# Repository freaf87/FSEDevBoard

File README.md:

Rpi Autonomous Car PCB 
====================
This board bring those additional functions below to the Raspberry pi:

	 - Analog Digital Converter with MCP3008 (8)
	 - DC Brushed Motor driver (2) with TB6612FNG
	 - Level converted IOs (5V <-> 3.3V) (8)
     - 16-channel, 12-bit PWM with PCA9685
     - RGB LED (1)
     - Pushbutton (1)

Top                                                                      |  Bottom
:-----------------------------------------------------------------------:|:--------------------------------------------------------------:
  |  

Author: Frederic Afadjigla, 2018

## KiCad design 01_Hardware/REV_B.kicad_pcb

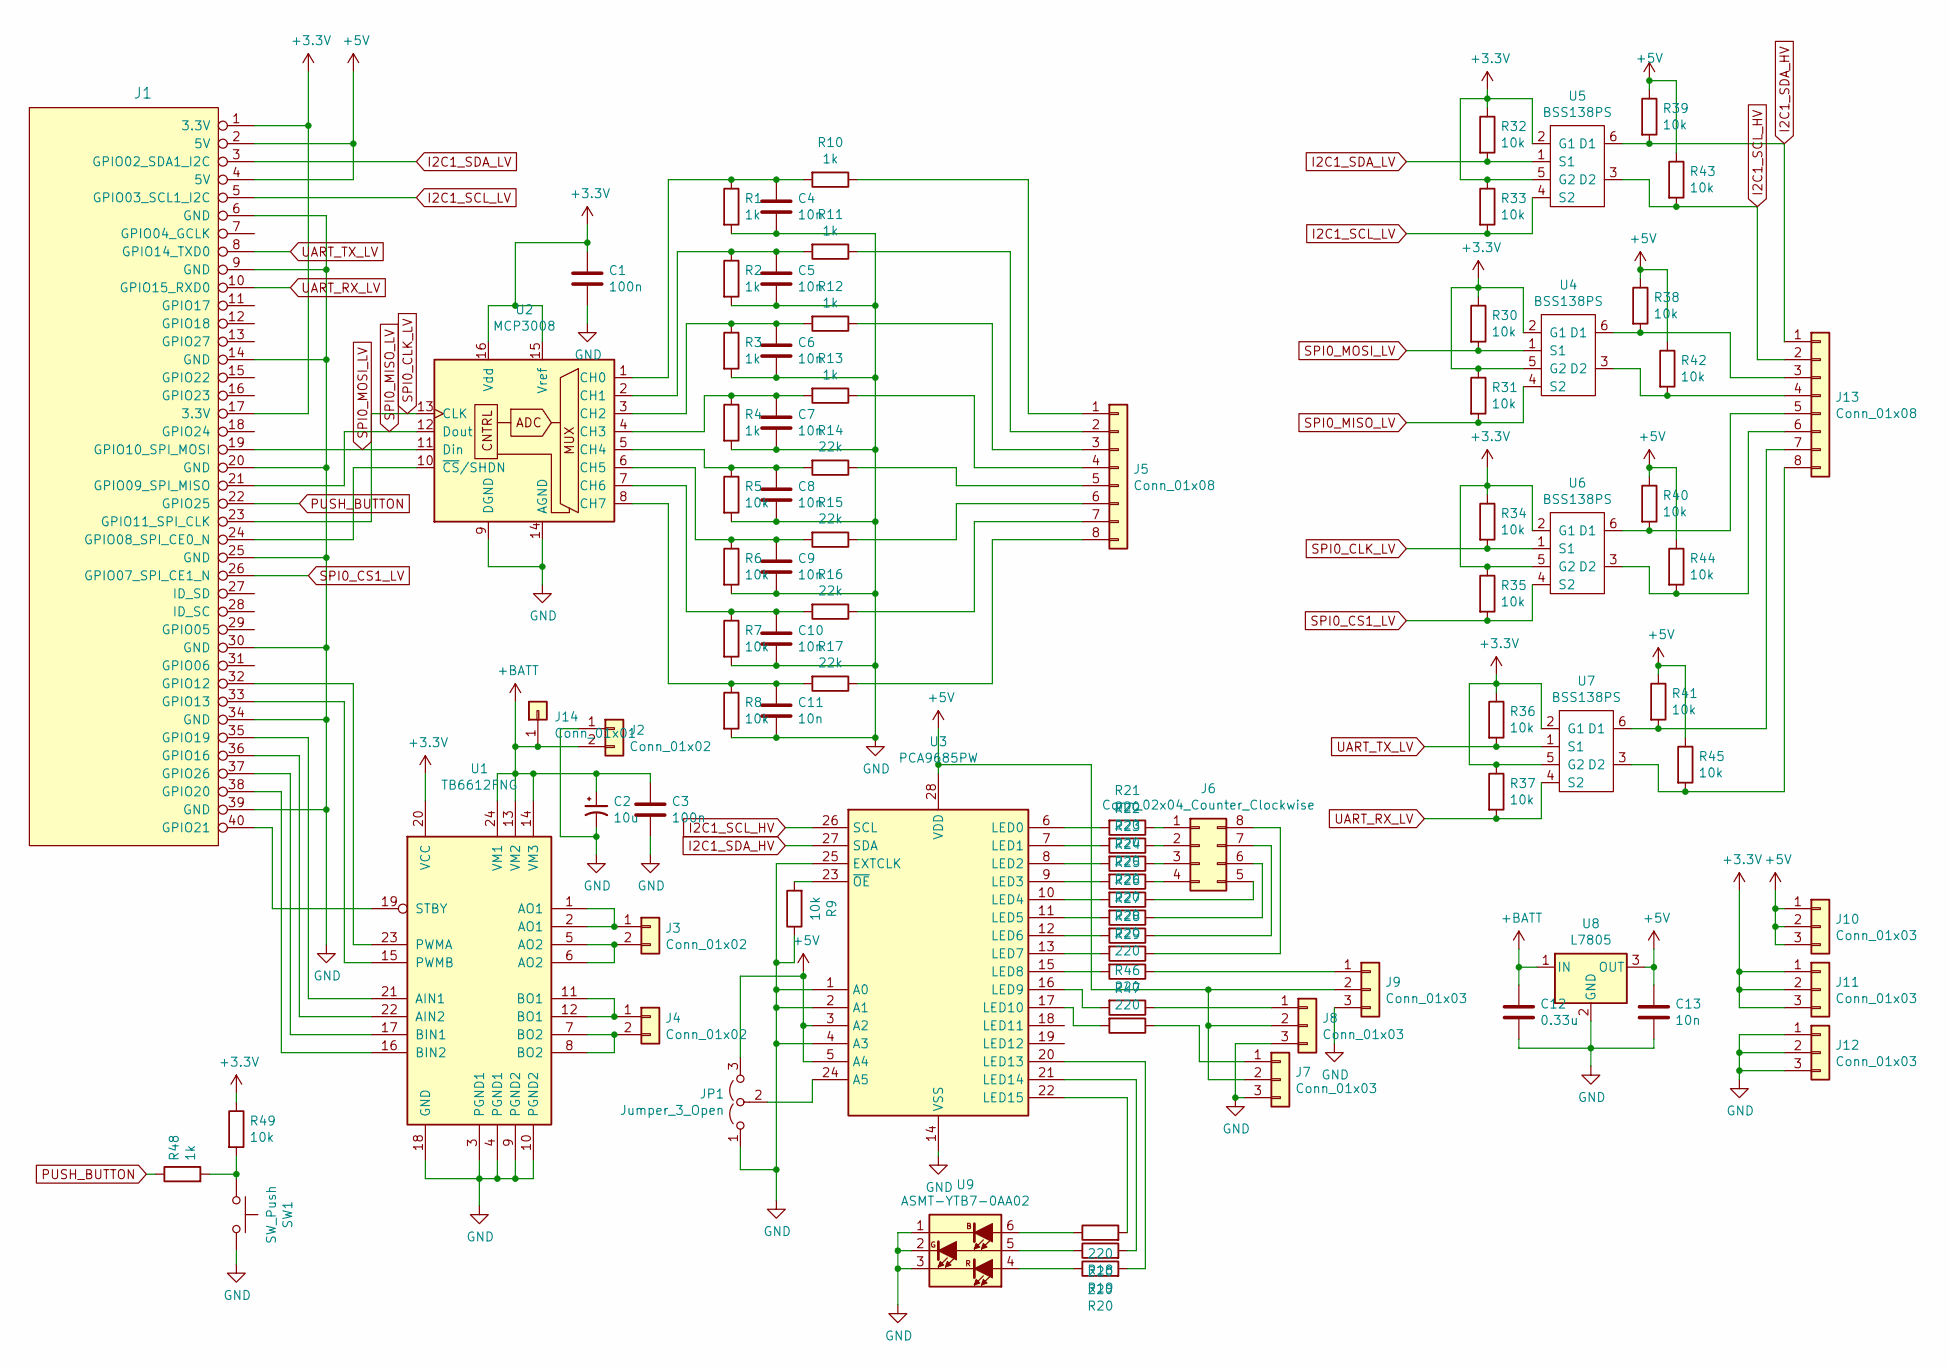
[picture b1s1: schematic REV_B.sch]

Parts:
C1, C3: 100n; C_0603_1608Metric
C2: 10u; CP_Elec_4x4.5
C4, C5, C6, C7, C8, C9, C10, C11, C13: 10n; C_0603_1608Metric
C12: 0.33u; C_0603_1608Metric
J1: RaspberryPi; PinSocket_2x20_P2.54mm_Vertical
J2, J3, J4: Conn_01x02; Molex_KK-254_AE-6410-02A_1x02_P2.54mm_Vertical
J5: Conn_01x08; PinHeader_1x08_P2.54mm_LongPad_Vertical_SMD_Pin1Right
J6: Conn_02x04_Counter_Clockwise; PinHeader_2x04_P2.54mm_Vertical_SMD
J7, J8, J9, J10, J11, J12: Conn_01x03; PinHeader_1x03_P2.54mm_Vertical
J13: Conn_01x08; PinHeader_1x08_P2.54mm_Vertical
J14: Conn_01x01; PinSocket_1x01_P2.54mm_Vertical
JP1: Jumper_3_Open; SolderJumper-3_P1.3mm_Open_RoundedPad1.0x1.5mm
R1, R2, R3, R4, R10, R11, R12, R13, R48: 1k; R_0603_1608Metric
R5, R6, R7, R8, R9, R30, R31, R32, R33, R34, R35, R36, R37, R38, R39, R40, R41, R42, R43, R44, R45, R49: 10k; R_0603_1608Metric
R14, R15, R16, R17: 22k; R_0603_1608Metric
R18, R19, R20, R21, R22, R23, R24, R25, R26, R27, R28, R29, R46, R47: 220; R_0603_1608Metric
SW1: SW_Push; SW_PUSH_6mm
U1: TB6612FNG; SSOP-24_5.3x8.2mm_P0.65mm
U2: MCP3008; SOIC-16_3.9x9.9mm_P1.27mm
U3: PCA9685PW; TSSOP-28_4.4x9.7mm_P0.65mm
U4, U5, U6, U7: BSS138PS; SOT-363_SC-70-6
U8: L7805; TO-252-3_TabPin2
U9: ASMT-YTB7-0AA02; LED_Avago_PLCC6_3x2.8mm

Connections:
+3V3: C1.1, J1.1 (3.3V), J1.17 (3.3V), J11.1, J11.2, J11.3, R30.1, R31.1, R32.1, R33.1, R34.1, R35.1, R36.1, R37.1, R49.1, U1.20 (VCC), U2.15 (Vref), U2.16 (Vdd), U4.2 (G1), U4.5 (G2), U5.2 (G1), U5.5 (G2), U6.2 (G1), U6.5 (G2), U7.2 (G1), U7.5 (G2)
+5V: C13.1, J1.2 (5V), J1.4 (5V), J7.2, J8.2, J9.2, J10.1, J10.2, J10.3, JP1.3 (B), R38.1, R39.1, R40.1, R41.1, R42.1, R43.1, R44.1, R45.1, U3.3 (A2), U3.5 (A4), U3.28 (VDD), U8.3 (OUT)
+BATT: C2.1, C3.1, C12.1, J2.2, J14.1, U1.13 (VM2), U1.14 (VM3), U1.24 (VM1), U8.1 (IN)
GND: C1.2, C2.2, C3.2, C4.2, C5.2, C6.2, C7.2, C8.2, C9.2, C10.2, C11.2, C12.2, C13.2, J1.6 (GND), J1.9 (GND), J1.14 (GND), J1.20 (GND), J1.25 (GND), J1.30 (GND), J1.34 (GND), J1.39 (GND), J2.1, J7.3, J8.3, J9.3, J12.1, J12.2, J12.3, JP1.1 (A), R1.2, R2.2, R3.2, R4.2, R5.2, R6.2, R7.2, R8.2, R9.1, SW1.2, U1.3 (PGND1), U1.4 (PGND1), U1.9 (PGND2), U1.10 (PGND2), U1.18 (GND), U2.9 (DGND), U2.14 (AGND), U3.1 (A0), U3.2 (A1), U3.4 (A3), U3.14 (VSS), U3.25 (EXTCLK), U8.2 (GND), U9.1 (KB), U9.2 (KG), U9.3 (KR)
I2C1_SCL_HV: J13.2, R43.2, U3.26 (SCL), U5.3 (D2)
I2C1_SCL_LV: J1.5 (GPIO03_SCL1_I2C), R33.2, U5.4 (S2)
I2C1_SDA_HV: J13.1, R39.2, U3.27 (SDA), U5.6 (D1)
I2C1_SDA_LV: J1.3 (GPIO02_SDA1_I2C), R32.2, U5.1 (S1)
unnamed: C4.1, R1.1, R10.2, U2.1 (CH0)
unnamed: C5.1, R2.1, R11.2, U2.2 (CH1)
unnamed: C6.1, R3.1, R12.2, U2.3 (CH2)
unnamed: C7.1, R4.1, R13.2, U2.4 (CH3)
unnamed: C8.1, R5.1, R14.2, U2.5 (CH4)
unnamed: C9.1, R6.1, R15.2, U2.6 (CH5)
unnamed: C10.1, R7.1, R16.2, U2.7 (CH6)
unnamed: C11.1, R8.1, R17.2, U2.8 (CH7)
unnamed: J1.24 (GPIO08_SPI_CE0_N), U2.10 (~CS~/SHDN)
unnamed: J1.32 (GPIO12), U1.23 (PWMA)
unnamed: J1.33 (GPIO13), U1.15 (PWMB)
unnamed: J1.35 (GPIO19), U1.21 (AIN1)
unnamed: J1.36 (GPIO16), U1.22 (AIN2)
unnamed: J1.37 (GPIO26), U1.17 (BIN1)
unnamed: J1.38 (GPIO20), U1.16 (BIN2)
unnamed: J1.40 (GPIO21), U1.19 (STBY)
unnamed: J3.1, U1.1 (AO1), U1.2 (AO1)
unnamed: J3.2, U1.5 (AO2), U1.6 (AO2)
unnamed: J4.1, U1.11 (BO1), U1.12 (BO1)
unnamed: J4.2, U1.7 (BO2), U1.8 (BO2)
unnamed: J5.1, R10.1
unnamed: J5.2, R11.1
unnamed: J5.3, R12.1
unnamed: J5.4, R13.1
unnamed: J5.5, R14.1
unnamed: J5.6, R15.1
unnamed: J5.7, R16.1
unnamed: J5.8, R17.1
unnamed: J6.1, R21.1
unnamed: J6.2, R22.1
unnamed: J6.3, R23.1
unnamed: J6.4, R24.1
unnamed: J6.5, R25.1
unnamed: J6.6, R26.1
unnamed: J6.7, R27.1
unnamed: J6.8, R28.1
unnamed: J7.1, R47.1
unnamed: J8.1, R46.1
unnamed: J9.1, R29.1
unnamed: J13.3, R38.2, U4.6 (D1)
unnamed: J13.4, R42.2, U4.3 (D2)
unnamed: J13.5, R40.2, U6.6 (D1)
unnamed: J13.6, R44.2, U6.3 (D2)
unnamed: J13.7, R41.2, U7.6 (D1)
unnamed: J13.8, R45.2, U7.3 (D2)
unnamed: JP1.2 (C), U3.24 (A5)
unnamed: R9.2, U3.23 (~OE)
unnamed: R18.1, U9.6 (AB)
unnamed: R18.2, U3.22 (LED15)
unnamed: R19.1, U9.5 (AG)
unnamed: R19.2, U3.21 (LED14)
unnamed: R20.1, U9.4 (AR)
unnamed: R20.2, U3.20 (LED13)
unnamed: R21.2, U3.6 (LED0)
unnamed: R22.2, U3.7 (LED1)
unnamed: R23.2, U3.8 (LED2)
unnamed: R24.2, U3.9 (LED3)
unnamed: R25.2, U3.10 (LED4)
unnamed: R26.2, U3.11 (LED5)
unnamed: R27.2, U3.12 (LED6)
unnamed: R28.2, U3.13 (LED7)
unnamed: R29.2, U3.15 (LED8)
unnamed: R46.2, U3.16 (LED9)
unnamed: R47.2, U3.17 (LED10)
unnamed: R48.2, R49.2, SW1.1
PUSH_BUTTON: J1.22 (GPIO25), R48.1
SPI0_CLK_LV: J1.23 (GPIO11_SPI_CLK), R34.2, U2.13 (CLK), U6.1 (S1)
SPI0_CS1_LV: J1.26 (GPIO07_SPI_CE1_N), R35.2, U6.4 (S2)
SPI0_MISO_LV: J1.21 (GPIO09_SPI_MISO), R31.2, U2.12 (Dout), U4.4 (S2)
SPI0_MOSI_LV: J1.19 (GPIO10_SPI_MOSI), R30.2, U2.11 (Din), U4.1 (S1)
UART_RX_LV: J1.10 (GPIO15_RXD0), R37.2, U7.4 (S2)
UART_TX_LV: J1.8 (GPIO14_TXD0), R36.2, U7.1 (S1)

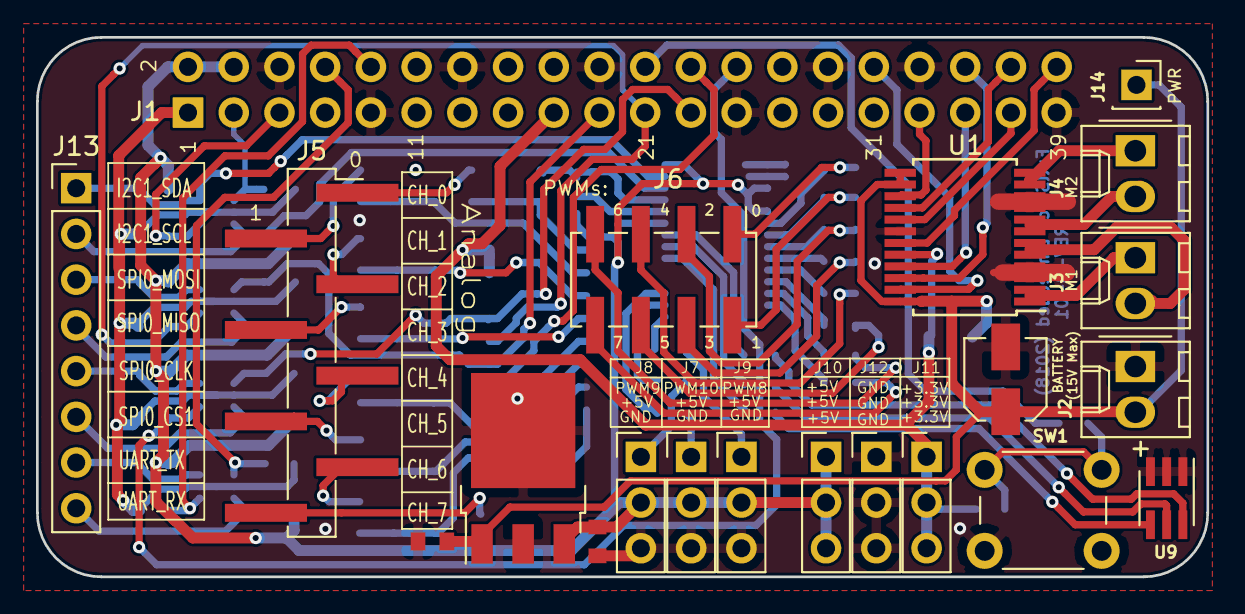
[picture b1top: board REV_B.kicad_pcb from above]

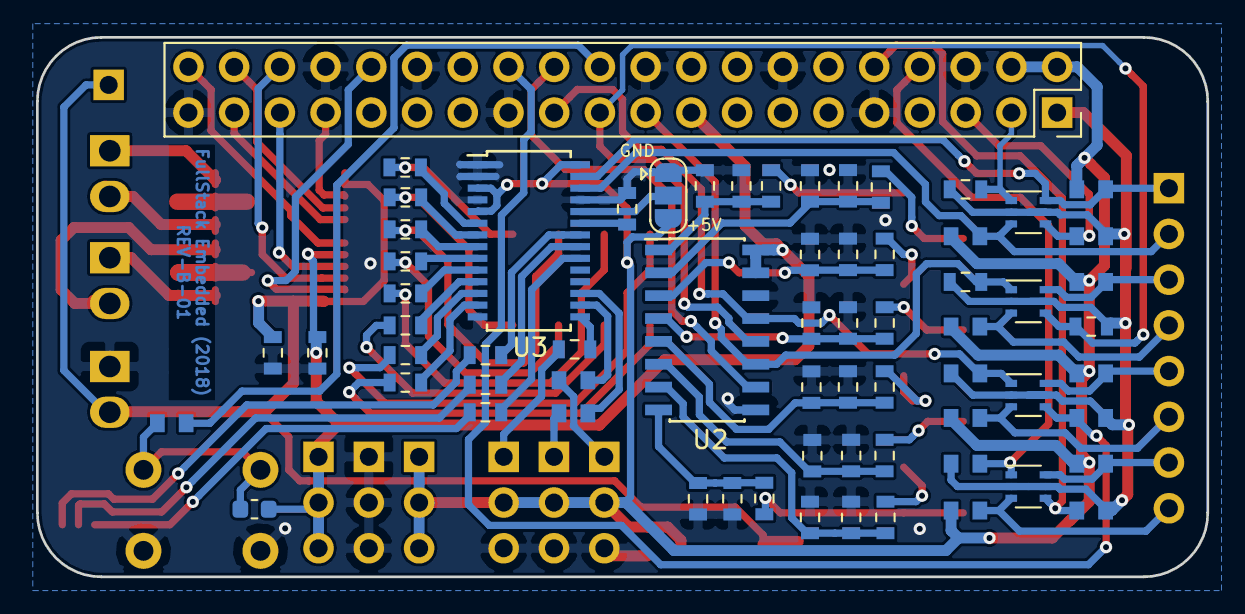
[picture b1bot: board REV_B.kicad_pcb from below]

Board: 2 copper layers, 65.0 x 30.0 mm, 87 parts (67 on the bottom side), 80 nets.

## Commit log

2018-12-12 RGB support added
2018-12-12 simplify LED interface a bit
2018-12-12 Ultrasonic module added
2018-12-12 Fix missing GND connection to PushButton
2018-12-12 pushbutton interface added
2018-12-13 buzzer, mcp3008, ultrasonic, pca9685 and rgb interfaces added
2018-12-14 first implementation of PDC.py
2018-12-14 Made /drivers python3 compatible
2018-12-14 rename lib folder to FSEDevBoard
2018-12-15 Packaging done
2018-12-15 Add buzzer support to PDC.py
2018-12-15 restructure a bit
2018-12-21 drivers made configurable
2018-12-22 Reference Manual initial revision
2018-12-23 working on Documentation
2019-01-04 PB Interface added
2019-01-04 change buzzer pin to GPIO4
2019-01-05 Motor driver tested ok
2019-01-05 Add instructions for executing using root in venv
2019-02-08 pdf doc regenerated
2019-07-07 LCD1602 and Rotary encoder support
